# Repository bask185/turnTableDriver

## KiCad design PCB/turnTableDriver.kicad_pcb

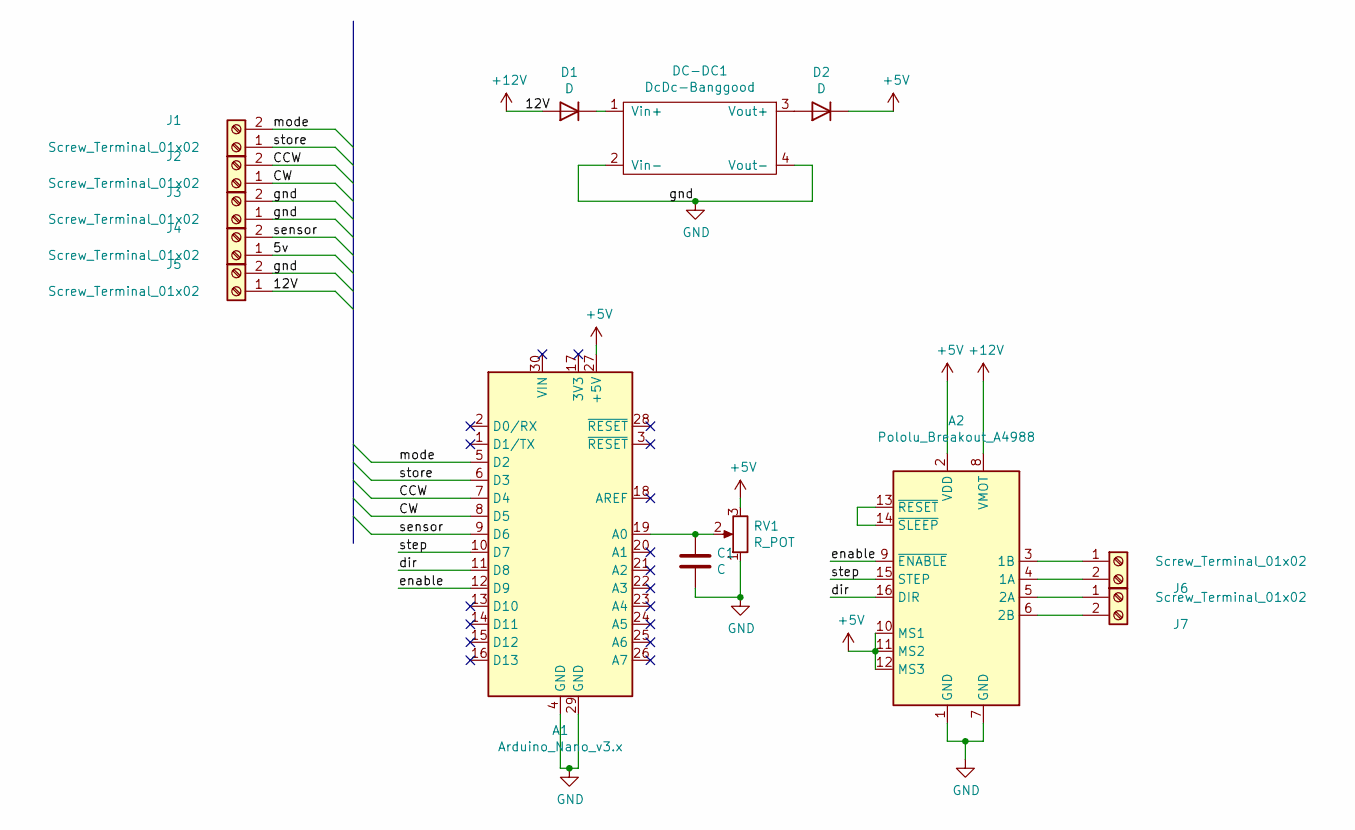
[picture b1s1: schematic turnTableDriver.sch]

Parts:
A1: Arduino_Nano_v3.x; Arduino_Nano
A2: Pololu_Breakout_A4988; Pololu_Breakout-16_15.2x20.3mm
C1: C; C_Disc_D4.7mm_W2.5mm_P5.00mm
D1, D2: D; D_A-405_P7.62mm_Horizontal
DC-DC1: DcDc-Banggood
J1, J2, J3, J4, J5, J6, J7: Screw_Terminal_01x02; TerminalBlock_bornier-2_P5.08mm
RV1: R_POT; Potentiometer_Runtron_RM-065_Vertical

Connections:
+5V: A1.27 (+5V), A2.2 (VDD), A2.10 (MS1), A2.11 (MS2), A2.12 (MS3), D2.1 (K), RV1.3
+12V: A2.8 (VMOT), D1.2 (A), J5.1
/5v: J4.1
/CCW: A1.7 (D4), J2.2
/CW: A1.8 (D5), J2.1
/dir: A1.11 (D8), A2.16 (DIR)
/enable: A1.12 (D9), A2.9 (~ENABLE)
/mode: A1.5 (D2), J1.2
/sensor: A1.9 (D6), J4.2
/step: A1.10 (D7), A2.15 (STEP)
/store: A1.6 (D3), J1.1
GND: A1.4 (GND), A1.29 (GND), A2.1 (GND), A2.7 (GND), C1.2, DC-DC1.2 (Vin-), DC-DC1.4 (Vout-), J3.1, J3.2, J5.2, RV1.1
unnamed: A1.19 (A0), C1.1, RV1.2
unnamed: A2.3 (1B), J6.1
unnamed: A2.4 (1A), J6.2
unnamed: A2.5 (2A), J7.1
unnamed: A2.6 (2B), J7.2
unnamed: A2.13 (~RESET), A2.14 (~SLEEP)
unnamed: D1.1 (K), DC-DC1.1 (Vin+)
unnamed: D2.2 (A), DC-DC1.3 (Vout+)

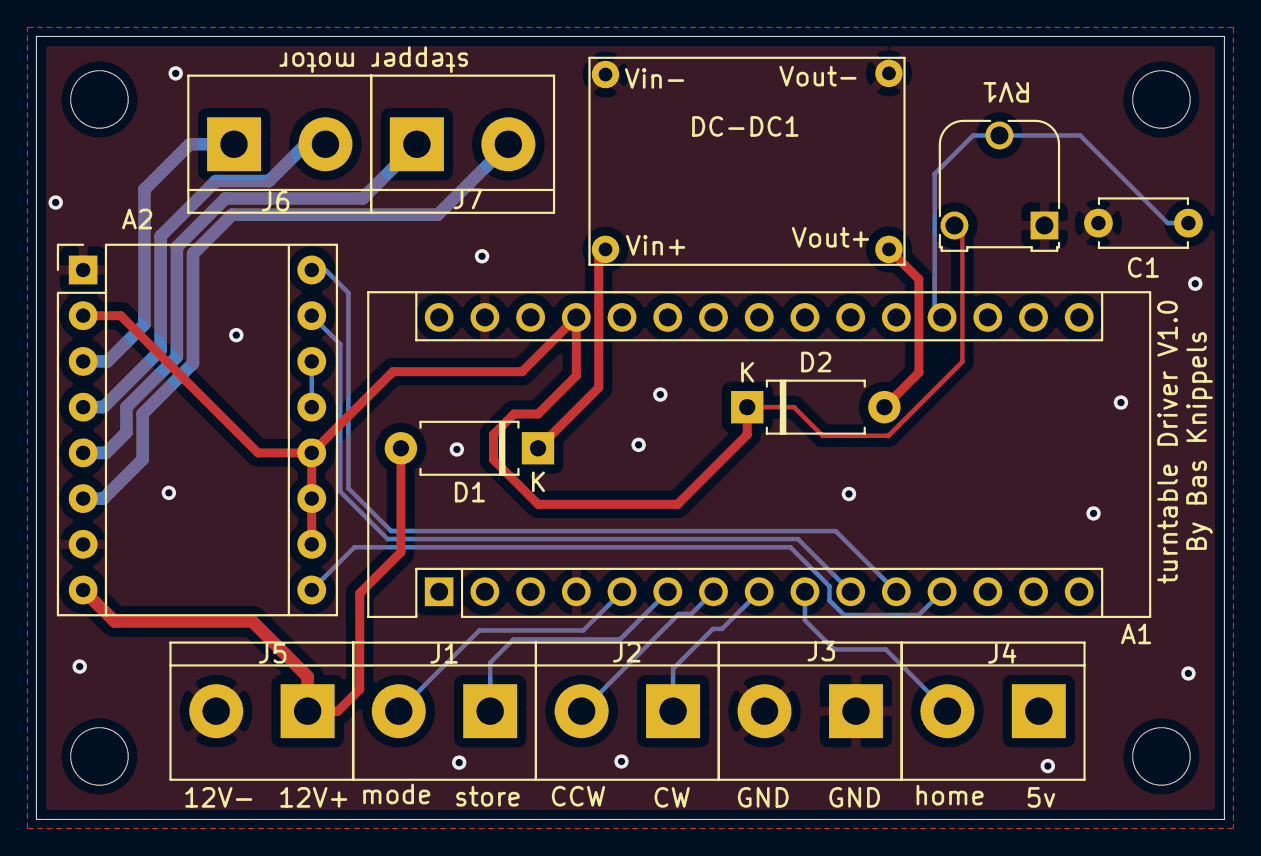
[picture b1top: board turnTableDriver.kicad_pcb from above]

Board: 2 copper layers, 66.0 x 43.5 mm, 14 parts (0 on the bottom side), 19 nets.

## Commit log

2021-08-17 added all files
2021-08-17 decided to do things easier. Most important code is now in .ino file. Idea is to first get the motor and menu system working and later alter the motor code with accel and decel. Code is not compiled 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
2021-08-17 project has been made compilable
2021-08-18 inputs are working, I had completely wrong IO numbering in place. I soldered the wire for nothing
2021-08-18 also fixed the output IO
2021-08-23 Most basis functionalities work. One can manually rotate the motor, one can store it's positions and one can shift to the positions in automatic mode.
    What is still lacking is remembering last set positions and loading these on startup
2021-08-23 merged files
2021-08-26 added 2 lines with comments. Speed should be calculated differently in manual mode
2021-11-12 added 2 files for the homing and measuring sequence
2021-11-14 commit for pull
2021-11-14 ditched the homing cycle files
2021-11-16 commit for push. Motor does not turn, though software works well further. Homing and measuring cycle works well
2021-11-21 Fixed the slot storing and shifting functions. The only thing which remains is the actual moving during shifting. Measure round and homing also work fine
2021-11-28 manual mode, storing, measuring and homing all works. Only the code for shifting steps in automatic mode does not
2022-01-27 added pcb files
